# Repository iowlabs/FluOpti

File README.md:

# FluOpti
Este proyecto consiste en la realización de un control integrado para la iluminación del proyecto FluOpti. Más información respecto al poyecto se puede encontrar en los siguientes enlaces:
1. https://docs.google.com/document/d/1PmyignsIkzQdomBdSQQ2lFlBKneosc83GTr52-iTTBQ/edit?usp=sharing
2. [Git](https://github.com/SynBioUC/FluoPi/tree/master/Hardware_design_files/PCB)
3. [OSF](https://osf.io/dy6p2/)
4. [Manual de diseño de proyectos de LEDs estandar](https://www.overleaf.com/4759732231nspqcngnnhdq)

## Descripción de problema electrónico
El sistema consiste en un dispositivo que permite observar muestras biológicas, a las cuales se les realizan procesos de activación genética por medio de otpogenética. 
En la práctica, el dispositivo consiste en una cámara conectada a una raspberry, la que permite observar las muestras, un set de LEDs, los que permiten realizar los procesos optogenéticos, y la respectiva electrónica de control. 

Los LEDs que se deben controlar realizan 3 tareas distintas:
1. Excitar la muestra para poder adquirir imágenes de fluorescencia: LEDs azules.
2. Iluminar la muestra para obtener imágenes de campo claro que permitan medir el crecimiento de las colonias bacterianas de manera apropiada: LEDs blancos.
3. Generar estímulos para activación de procesos optogenéticos. Estos LEDs son de longitudes de onda específicas dependiendo del gen que se desee activar/desactivar: LEDs rojos y verdes.

El proyecto también considera la necesidad de implementar sensores que permitan calibrar el sistema y monitorear variables determinadas, tales como intensidad o temperatura.

## Requerimientos

### Requerimientos generales
A continuación se enlista un set de requerimientos generales del proyecto:
1. Implementar una electrónica compatible con los componentes actuales disponibles.
2. Proponer una solución completa al problema.
3. Considerar diseños modulares que permitan adaptarse a parámetros futuros.

### Requerimientos específicos

A continuación se enlista un set de requerimientos específicos del proyecto:
1. Los LEDs azules empleados para iluminar la muestra corresponden a los [Super Bright 5mm Blue](https://www.superbrightleds.com/moreinfo/through-hole/5mm-blue-led-120-degree-viewing-angle-flat-tipped-1200-mcd/265/1192/):
   * Longitud de onda: 470nm
   * Forward current: 30mA @ 3.3V
   * Peak forward current: 100mA
   * Max voltage forward: 3.8V
   
2. Actualmente, se está pensando en una placa de LEDs azules con distribución física del tipo circular. Esto implicaría una cantidad de 55 LEDs. En la siguiente imagen se muestra esta topología propuesta:

3. Los LEDs verdes empleados para la activación de genes corresponden a los [Kingbright WP7083ZGD/G](http://www.kingbrightusa.com/images/catalog/SPEC/WP7083ZGD-G.pdf):
   * Longitud de onda: 520nm
   * Forward current (typ): 20mA @ 3.2V
   * Peak forward current: 100mA
   * Max voltage forward: 4V
   
4. Los LEDs rojos empleados para la desactivación de genes corresponden a los [Deep-Red 5mm LED](https://www.ledsupply.com/leds/5mm-led-deep-red-660nm-50-degree-viewing-angle):
   * Longitud de onda: 660nm
   * Forward current (typ): 20mA @ 2.2V
   * Peak forward current: 100mA
   * Max voltage forward: 2.8V
   
5. Los LEDs blancos se implementan por medio de una tira LED comercial. Típicamente su operación se caracteriza por:
   * Forward current: 20mA @ 12V
   
6. El control implementado debe corresponder a PWM, con el fin de regular la intensidad lumínica de los LEDs. Se opta por este control debido a su sencilla implementación.

7. El sistema  debe contar con un sistema de distribución de potencia para alimentar todos los sub-módulos, LEDs y raspberry.

8. El sistema debe contar, además, con la posibilidad de leer sensores que permitan medir y calibrar la intensidad de luz proveniente desde los LEDs. Dado que el control se implementa por medio de una raspberry, es necesario utilizar sensores digitales o incluir en el diseño un ADC que permita realizar la conversión. En este último caso será necesaria la inclusión de una etapa que acondicione las señales provenientes desde los sensores.
   
9. El sensor de intensidad lumínica tiene que cumplir:
* Bajo costo
* Fácil de conseguir
* Respuesta plana para los LED Rojo y Verde

Una alternativa es el fototransistor [TEMT6000](https://learn.sparkfun.com/tutorials/temt6000-ambient-light-sensor-hookup-guide/all).

10. El sensor de temperatura es un NTC (termistor). [Aquí](https://www.adafruit.com/product/372) se presenta una alternativa.

11. El heater es del tipo resistivo y se debe poder alimentar con 9V ó 12V. Se debe implementar un control PWM de corriente utilizando un transistor. Una posible alternativa de heater es el [Film Heating Panel](http://www.icstation.com/heating-thin-film-polyimide-heating-plate-panel-25x50mm-b1221-p-9887.html).

### Consideraciones de diseño adicionales
   
1. Consideraciones de operación: El dispositivo debe ser diseñado para funcionar en espacios interiores y dentro de una cápsula cerrada, en la se realiza el análisis de las muestras, por lo que no es necesaria la resistencia al agua o a condiciones de humedad extremas. La placa estará, además, dentro de una caja, por lo que tampoco estará expuesta a polvo u otros contaminantes. Una vez instalado el dispositivo, este permanecerá siempre en el mismo lugar (a menos que se deba extraer por alguna situación en particular), por lo que no es necesario que el diseño considere la exposición a posibles golpes o vibraciones muy significativas.

2. La única etapa del circuito que puede significar un peligro para el usuario es la alimentación, puesto que esta proviene desde la red eléctrica, por lo cual es prudente que la carcasa del producto cumpla con normas acorde al voltaje y corriente de operación, por ejemplo, IP67. Sin embargo, esta protección será ajena al circuito mismo. Es pertinente, de todas formas, la inclusión de disipadores en algunos integrados, en el caso que operen con altas corrientes. Esto, para evitar fallas durante la operación o incluso que se quemen componentes.

## Propuesta
Teniendo presente los requerimientos planteados en la sección anterior se propone una solución basada en el siguiente esquema

El principal criterio de diseño considerado es la modularidad, con el objetivo de poder entregar una solución adaptable y escalable. Los parámetros prácticos de elección de componentes dependen de los requerimientos específicos del sistema. El esquema general consiste en un módulo que genera señales PWM, el cual es controlado por protocolo serial I2C. Este módulo genera 16 señales de PWM permitiendo controlar hasta 16 canales. Estas señales PWM controlan los módulos driver. Estos últimos ajustan la señal PWM a los requerimientos que necesitan los distintos tipos de circuitos de LEDs. Cada driver puede poseer uno o más canales dependiendo de la cantidad de subcircuitos independientes que se deseen controlar por tipo de LED. Del mismo modo, algunas de estas señales de control PWM pueden dejarse a disposición del usuario en caso que necesite controlar una placa con driver ya existente, como es el caso de este proyecto. 

El otro bloque importante es el sistema de distribución de poder, el cual se encarga de generar todos los voltajes necesarios para los distintos bloques y etapas del circuito, dependiendo de cada requerimiento. La idea principal es que la placa reciba una única alimentación y que, internamente, genere los distintos voltajes y corrientes, contribuyendo, así, a la adaptabilidad de la solución.

Por último, la placa considera la inclusión de un ADC de 4 canales, controlado por I2C, el cual permite leer hasta 4 sensores analógicos. Es necesario contar con un ADC, ya que la Raspberry Pi no cuenta con ADC. Esto permite otorgar una alta adaptabilidad, ya que es posible conectar distintos tipos de sensores analógicos, dependiendo de la aplicación. Para esto, la placa considera etapas de acondicionamiento de señal, las cuales se deben configurar para el sensor específico.

### Resumen de características de la solución propuesta

Las principales características de la solución propuesta son:

1. Adaptabilidad: La placa total solo se controla por medio de un bus I2C (3 pines), independiente de la cantidad de LEDs y sensores que se deseen utilizar. 

2. Integración: La disposición de canales de control PWM permite integrar tanto las soluciones existentes como soluciones creadas por distintos fabricantes.

3. Escalabilidad: Gracias a la utilización del protocolo I2C, es posible controlar múltiples de estas placas con una sola Raspberry Pi (o un solo microcontrolador/procesador en general). Si se integran dos placas en serie se puede llegar a disponer de 32 canales de control de LEDs y 8 canales de sensores analógicos. 

A continuación, se describen en detalle los módulos a implementar. Es importante mencionar que se utilizó como guía el [documento tutorial](https://www.overleaf.com/4759732231nspqcngnnhdq) generado en el marco de este proyecto.

### Detalle de módulos

#### ADC
El ADC escogido es el [ADC](https://cdn-shop.adafruit.com/datasheets/ads1115.pdf) de la empresa Texas Instruments. La empresa [adafruit](https://www.adafruit.com/product/1085) posee un módulo autocontenido para integrar este ADC a la Raspberry Pi, así como una completa documentación y las bibliotecas para utilizarlo. 

Las principales características de este ADC se enlistan a continuación

* 4 canales, single-ended.
* 16 bits de resolución
* Voltaje de alimentación entre 2V a 5V
* Interfaz I2C
* Referencia interna

#### Acondicionamiento de señal
Los sensores que se utilizarán permiten implementar el proceso de medición gracias a la variación de sus propiedades eléctricas. En general, estas variaciones se evidencian mediante un cambio de voltaje. En consecuencia, este es el voltaje que debe ser adquirido por el circuito electrónico. Por ello, en primera instancia, se dispone de un circuito divisor que, al ser conectado con el respectivo sensor, permite obtener el voltaje asociado a la medición. En la siguiente figura se muestra un ejemplo de esta conexión circuital, para el caso de un sensor de temperatura del tipo termistor (NTC):

Para realizar correctamente la adquisición de las señales desde los sensores es necesario contar con una etapa de acondicionamiento de señal. De esta forma, se asegura que los valores de voltaje que entreguen los sensores se encuentren dentro de los límites que permiten las entradas del ADC y de la Raspberry. No solo es deseable que se opere dentro de los límites, sino también aprovechar el rango de lectura al máximo, es decir, que el voltaje mínimo de medición sea igual (o lo más cercano posible) al voltaje mínimo que permiten los pines del ADC. Y, la misma relación con el voltaje máximo de medición. 

Dado que aún no existe 100% de certeza sobre los sensores a utilizar, se implementó una circuito genérico de acondicionamiento, el cual se compone de una etapa de amplificación y otra de adición de offset. En la siguiente figura se muestra este circuito:

Los símbolos de switches corresponden, en la práctica, a un solder jumper, el cual conecta la entrada con la salida solo si se unen con soldadura sus terminales. Si se conectan S1, S2 y S3 el circuito queda configurado como un buffer, lo cual, de todas formas, beneficia a la señal adquirida puesto que el buffer disminuye su impedancia. Conectando o no S1, S2 y S3 se pueden obtener distintas configuraciones: solo amplificador, solo adición de offset, o ambas. Además, los valores de las resistencias se pueden ajustar dependiendo de los sensores que se utilicen, de tal forma de fijar correctamente la ganancia y el offset, según sea el caso.

#### Generador de PWM
La generación de PWM se realiza por medio de un circuito integrado [PCA9685](https://cdn-shop.adafruit.com/datasheets/PCA9685.pdf). La empresa [adafruit](https://www.adafruit.com/product/2928) posee un módulo autocontenido para integrar este módulo a la Raspberry Pi, así como una documentación completa y las bibliotecas para utilizarlo. 

Principales características:

* 16 canales dimeables por PWM.
* 12 bits de resolución
* Voltaje de alimentación etre 2.3V a 5.5V
* Interfaz I2C

#### Driver de baja corriente

Para los canales de bajo consumo de corriente, tales como los arreglos de LEDs rojos y verdes, se utilizará el integrado [ULN2803](https://www.electroschematics.com/wp-content/uploads/2013/07/uln2803a-datasheet.pdf). Este integrado implementa un arreglo de 8 transistores tipo darlington, haciendo posible el control de hasta 8 canales en un único integrado.

Principales características:

* Arreglo de 8 canales
* Poseen alimentación común
* La corriente máxima por canal es de 500mA, pudiendo aumentar esta cantidad si se consideran canales en paralelo.

#### Driver de alta corriente
Para los canales de alto consumo se utilizará un transistor mosfet [IRF740](https://datasheet.lcsc.com/szlcsc/1808281645_Infineon-Technologies-IRF7402TRPBF_C169089.pdf). Es necesario contar con un transistor por canal. Y, para casos de alta corriente (superiores a 1A) es necesario considerar la inclusión de disipadores (heatsink) o pads de disipación que permitan una evacuación efectiva del calor.

Principales características:

* Altas frecuencias de switching
* Bajo consumo de operación 
* Control de hasta 10A (ó 40A en corrientes pulsantes)
* Simple implementación

#### Sistema de distribución de poder

Como se mencionará más adelante, la alimentación que llegará al circuito electrónico implementado será de 12VDC, por lo que es necesario contar con convertidores de voltaje DC-DC para generar los distintos voltajes de alimentación que se requieren en el circuito. En particular, es necesario generar 5V y 3.3V para alimentar los circuitos analógicos y digitales, y un set de voltajes para alimentar los distintos arreglos de LEDs y el Heater. Se decidió disponer de los siguientes voltajes para este último uso: 9V, 16V, 20V y 24V. A continuación se especifican los convertidores empleados para generar cada uno de los voltajes mencionados.

##### 5V
* Integrado: [LM2596R-5.0](https://datasheet.lcsc.com/szlcsc/1811131510_HTC-Korea-TAEJIN-Tech-LM2596R-5-0_C77782.pdf)
* Tipo: Step-down, regulador switching
* Frecuencia de switcheo: 150kHz
* Corriente máxima de salida: 3A

##### 3.3V
* Integrado: [AP2112K-3.3](https://datasheet.lcsc.com/szlcsc/1809192242_Diodes-Incorporated-AP2112K-3-3TRG1_C51118.pdf)
* Tipo: LDO, regulador lineal
* Corriente máxima de salida: 600mA

##### 9V
* Integrado: [LM2696SX-ADJ](https://datasheet.lcsc.com/szlcsc/1809192335_Texas-Instruments-LM2596SX-ADJ-NOPB_C29781.pdf)
* Tipo: Step-down, regulador switching ajustable (voltaje de salida es configurable según indicaciones de conexión en el datasheet)
* Frecuencia de switcheo: 150kHz
* Corriente máxima de salida: 3A

##### 16V, 20V, 24V
* Integrado: [XL6008E1](https://datasheet.lcsc.com/szlcsc/1809200019_XLSEMI-XL6008E1_C73012.pdf)
* Tipo: Step-up, regulador switching ajustable (voltaje de salida es configurable según indicaciones de conexión en el datasheet)
* Frecuencia de switcheo: 400kHz
* Corriente máxima de salida: 3A

#### Fuente de alimentación

Dado que el circuito electrónico funcionará con alimentación DC es necesario emplear una fuente DC que se enchufe directamente a la red y que entegue un voltaje de salida continuo. En particular, se decidió emplear una [fuente DC conmutada](https://afel.cl/producto/fuente-de-poder-12v-10a-120w/). Sus principales características son:

* Voltaje de entrada: 100-120VAC / 60Hz, **200-240VAC / 50Hz**
* Voltaje de salida: 12V
* Corriente máxima de salida: 10A
* Potencia máxima de salida: 120W

## Esquemático

En la siguiente figura se muestra el diagrama de bloques del esquemático implementado

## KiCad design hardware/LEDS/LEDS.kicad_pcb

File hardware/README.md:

# FluOpti Electrónica

FluOpti es una dispositivo controlador de LEDs para aplicaciones optogenéticas dentro del contexto del proyecto FluOpti.

La placa desarrollada contiene la electrónica necesaria para controlar fuentes de iluminación de alto consumo basadas en LEDS. Dependiendo de la cantidad de LEDs utilizadas y el tipo de conexión en que se dispongan estas matrices de LEDs pueden variar tanto en consumo como el el voltaje de operación.

Es por esto que la electrónica diseñada fue desarrollada considerando flexibilidad en su implementación para abordar un gran  numero de escenarios.

Cuenta con 4 canales de alta potencia para aborar cargas de 24 20 16 12 V configurables y potencias de ahasta

### Features

 La placa cuenta principalmente con 4 canales para controlar canales de LEDS

 - Canal de alta potencia para LEDs azules
 - 3 canales de baja potencia para LEDs Rojos, Verdes, Blancas.

Adicionalmente la placa implementa un controlador de temperatura, para esto cuenta con la electrónica necesaria para drivear 2 heaters resistivos, y con la capacidad de conectar hasta 4 sensores de temperatura NTC analógicos.

## Descripción de Hardware

El esquema presentado en la siguiente figura presenta una descripción general de la estructura del hardware desarrollado.  

El principal criterio de diseño considerado es la modularidad, con el objetivo de poder entregar una solución adaptable y escalable. El esquema general consiste en un módulo que genera señales PWM, el cual es controlado por protocolo serial I2C. Este módulo genera 16 señales de PWM permitiendo controlar hasta 16 canales. Estas señales PWM controlan los módulos driver que se encargan de adaptarse a los requerimientos de corriente y voltaje de las cargas asociadas. Cada driver puede poseer uno o más canales dependiendo de la cantidad de subcircuitos independientes que se deseen controlar por tipo de LED. Del mismo modo, algunas de estas señales de control PWM fueron dejadas a disposición del usuario en caso que necesite controlar una placa con driver ya existente, como es el caso de este proyecto (compatibilidad con diseños anteriores).

El otro bloque importante es el sistema de distribución de poder, el cual se encarga de generar todos los voltajes necesarios para los distintos bloques y etapas del circuito, dependiendo de cada requerimiento. La idea principal es que la placa reciba una única alimentación y que, internamente, genere los distintos voltajes y corrientes, contribuyendo, así, a la adaptabilidad de la solución.

Por último, la placa considera la inclusión de un ADC de 4 canales, controlado por I2C, el cual permite leer hasta 4 sensores analógicos para implementar los sensores de corriente. Es necesario contar con un ADC, ya que la Raspberry Pi no cuenta con ADC. Esto permite otorgar una alta adaptabilidad, ya que es posible conectar distintos tipos de sensores analógicos, dependiendo de la aplicación. Para esto, la placa considera etapas de acondicionamiento de señal, las cuales se deben configurar para el sensor específico.

### Resumen de características de la solución propuesta

Las principales características de la solución propuesta son:

1. Adaptabilidad: La placa total solo se controla por medio de un bus I2C (3 pines), independiente de la cantidad de LEDs y sensores que se deseen utilizar.

2. Integración: La disposición de canales de control PWM permite integrar tanto las soluciones existentes como soluciones creadas por distintos fabricantes.

3. Escalabilidad: Gracias a la utilización del protocolo I2C, es posible controlar múltiples de estas placas con una sola Raspberry Pi (o un solo microcontrolador/procesador en general). Si se integran dos placas en serie se puede llegar a disponer de 32 canales de control de LEDs y 8 canales de sensores analógicos.

A continuación, se describen en detalle los módulos a implementar. Es importante mencionar que se utilizó como guía el [documento tutorial](https://www.overleaf.com/4759732231nspqcngnnhdq) generado en el marco de este proyecto.

### Detalle de módulos

#### ADC
El ADC escogido es el [ADC](https://cdn-shop.adafruit.com/datasheets/ads1115.pdf) de la empresa Texas Instruments. La empresa [adafruit](https://www.adafruit.com/product/1085) posee un módulo autocontenido para integrar este ADC a la Raspberry Pi, así como una completa documentación y las bibliotecas para utilizarlo.

Las principales características de este ADC se enlistan a continuación

* 4 canales, single-ended.
* 16 bits de resolución
* Voltaje de alimentación entre 2V a 5V
* Interfaz I2C
* Referencia interna

#### Acondicionamiento de señal
Los sensores que se utilizarán permiten implementar el proceso de medición gracias a la variación de sus propiedades eléctricas. En general, estas variaciones se evidencian mediante un cambio de voltaje. En consecuencia, este es el voltaje que debe ser adquirido por el circuito electrónico. Por ello, en primera instancia, se dispone de un circuito divisor que, al ser conectado con el respectivo sensor, permite obtener el voltaje asociado a la medición. En la siguiente figura se muestra un ejemplo de esta conexión circuital, para el caso de un sensor de temperatura del tipo termistor (NTC):

Para realizar correctamente la adquisición de las señales desde los sensores es necesario contar con una etapa de acondicionamiento de señal. De esta forma, se asegura que los valores de voltaje que entreguen los sensores se encuentren dentro de los límites que permiten las entradas del ADC y de la Raspberry. No solo es deseable que se opere dentro de los límites, sino también aprovechar el rango de lectura al máximo, es decir, que el voltaje mínimo de medición sea igual (o lo más cercano posible) al voltaje mínimo que permiten los pines del ADC. Y, la misma relación con el voltaje máximo de medición.

Dado que aún no existe 100% de certeza sobre los sensores a utilizar, se implementó una circuito genérico de acondicionamiento, el cual se compone de una etapa de amplificación y otra de adición de offset. En la siguiente figura se muestra este circuito:

Los símbolos de switches corresponden, en la práctica, a un solder jumper, el cual conecta la entrada con la salida solo si se unen con soldadura sus terminales. Si se conectan S1, S2 y S3 el circuito queda configurado como un buffer, lo cual, de todas formas, beneficia a la señal adquirida puesto que el buffer disminuye su impedancia. Conectando o no S1, S2 y S3 se pueden obtener distintas configuraciones: solo amplificador, solo adición de offset, o ambas. Además, los valores de las resistencias se pueden ajustar dependiendo de los sensores que se utilicen, de tal forma de fijar correctamente la ganancia y el offset, según sea el caso.

#### Generador de PWM
La generación de PWM se realiza por medio de un circuito integrado [PCA9685](https://cdn-shop.adafruit.com/datasheets/PCA9685.pdf). La empresa [adafruit](https://www.adafruit.com/product/2928) posee un módulo autocontenido para integrar este módulo a la Raspberry Pi, así como una documentación completa y las bibliotecas para utilizarlo.

Principales características:

* 16 canales dimeables por PWM.
* 12 bits de resolución
* Voltaje de alimentación etre 2.3V a 5.5V
* Interfaz I2C

#### Driver de baja corriente

Para los canales de bajo consumo de corriente, tales como los arreglos de LEDs rojos y verdes, se utilizará el integrado [ULN2803](https://www.electroschematics.com/wp-content/uploads/2013/07/uln2803a-datasheet.pdf). Este integrado implementa un arreglo de 8 transistores tipo darlington, haciendo posible el control de hasta 8 canales en un único integrado.

Principales características:

* Arreglo de 8 canales
* Poseen alimentación común
* La corriente máxima por canal es de 500mA, pudiendo aumentar esta cantidad si se consideran canales en paralelo.

#### Driver de alta corriente
Para los canales de alto consumo se utilizará un transistor mosfet [IRF740](https://datasheet.lcsc.com/szlcsc/1808281645_Infineon-Technologies-IRF7402TRPBF_C169089.pdf). Es necesario contar con un transistor por canal. Y, para casos de alta corriente (superiores a 1A) es necesario considerar la inclusión de disipadores (heatsink) o pads de disipación que permitan una evacuación efectiva del calor.

Principales características:

* Altas frecuencias de switching
* Bajo consumo de operación
* Control de hasta 10A (ó 40A en corrientes pulsantes)
* Simple implementación

#### Sistema de distribución de poder

Como se mencionará más adelante, la alimentación que llegará al circuito electrónico implementado será de 12VDC, por lo que es necesario contar con convertidores de voltaje DC-DC para generar los distintos voltajes de alimentación que se requieren en el circuito. En particular, es necesario generar 5V y 3.3V para alimentar los circuitos analógicos y digitales, y un set de voltajes para alimentar los distintos arreglos de LEDs y el Heater. Se decidió disponer de los siguientes voltajes para este último uso: 9V, 16V, 20V y 24V. A continuación se especifican los convertidores empleados para generar cada uno de los voltajes mencionados.

##### 5V
* Integrado: [LM2596R-5.0](https://datasheet.lcsc.com/szlcsc/1811131510_HTC-Korea-TAEJIN-Tech-LM2596R-5-0_C77782.pdf)
* Tipo: Step-down, regulador switching
* Frecuencia de switcheo: 150kHz
* Corriente máxima de salida: 3A

##### 3.3V
* Integrado: [AP2112K-3.3](https://datasheet.lcsc.com/szlcsc/1809192242_Diodes-Incorporated-AP2112K-3-3TRG1_C51118.pdf)
* Tipo: LDO, regulador lineal
* Corriente máxima de salida: 600mA

##### 9V
* Integrado: [LM2696SX-ADJ](https://datasheet.lcsc.com/szlcsc/1809192335_Texas-Instruments-LM2596SX-ADJ-NOPB_C29781.pdf)
* Tipo: Step-down, regulador switching ajustable (voltaje de salida es configurable según indicaciones de conexión en el datasheet)
* Frecuencia de switcheo: 150kHz
* Corriente máxima de salida: 3A

##### 16V, 20V, 24V
* Integrado: [XL6008E1](https://datasheet.lcsc.com/szlcsc/1809200019_XLSEMI-XL6008E1_C73012.pdf)
* Tipo: Step-up, regulador switching ajustable (voltaje de salida es configurable según indicaciones de conexión en el datasheet)
* Frecuencia de switcheo: 400kHz
* Corriente máxima de salida: 3A

#### Fuente de alimentación

Dado que el circuito electrónico funcionará con alimentación DC es necesario emplear una fuente DC que se enchufe directamente a la red y que entegue un voltaje de salida continuo. En particular, se decidió emplear una [fuente DC conmutada](https://afel.cl/producto/fuente-de-poder-12v-10a-120w/). Sus principales características son:

* Voltaje de entrada: 100-120VAC / 60Hz, **200-240VAC / 50Hz**
* Voltaje de salida: 12V
* Corriente máxima de salida: 10A
* Potencia máxima de salida: 120W

## Esquemático

En la siguiente figura se muestra el diagrama de bloques del esquemático implementado

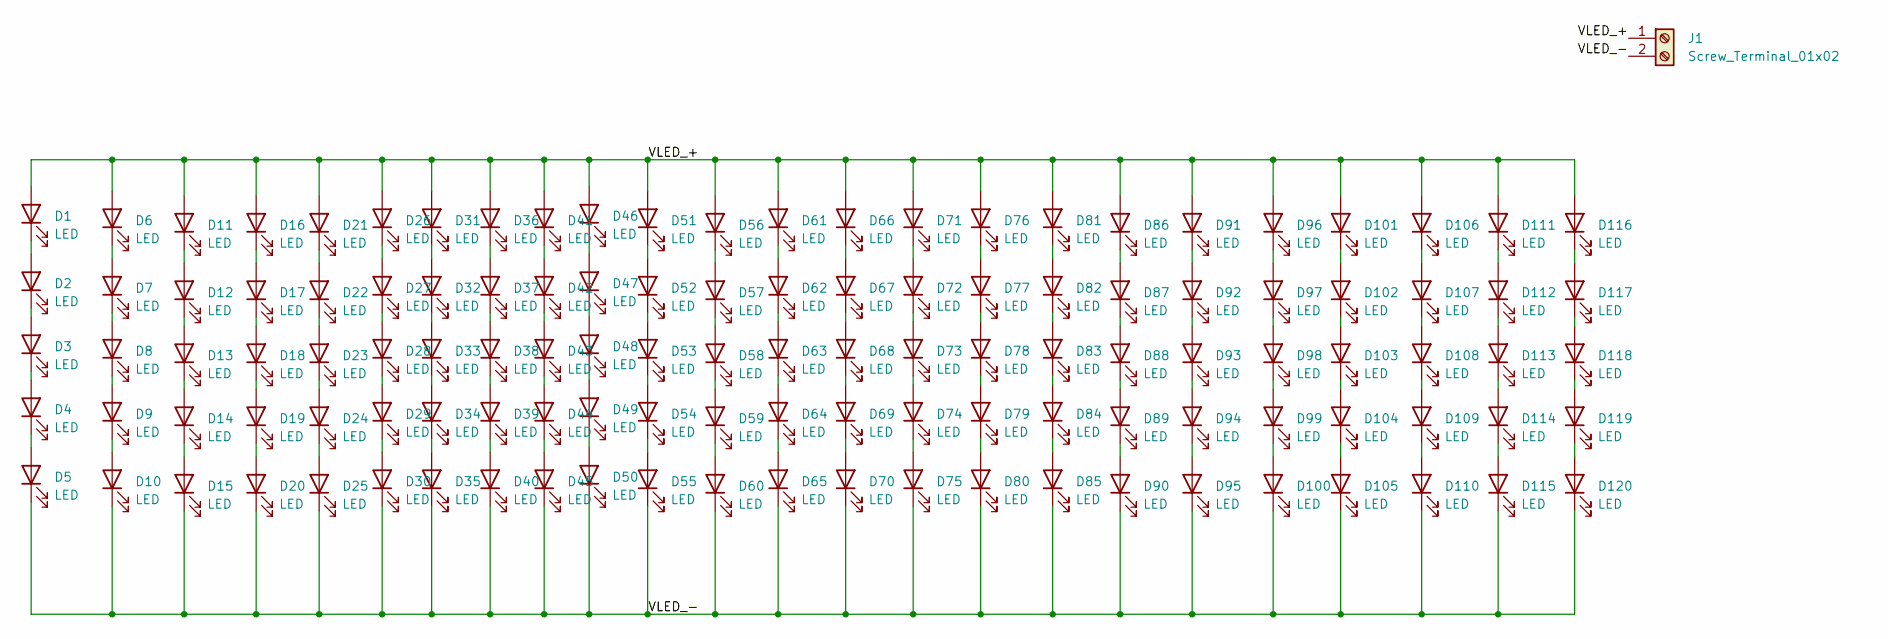
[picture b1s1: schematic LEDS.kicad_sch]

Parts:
D1, D2, D3, D4, D5, D6, D7, D8, D9, D10, D11, D12, D13, D14, D15, D16, D17, D18, D19, D20, D21, D22, D23, D24, D25, D26, D27, D28, D29, D30, D31, D32, D33, D34, D35, D36, D37, D38, D39, D40, D41, D42, D43, D44, D45, D46, D47, D48, D49, D50, D51, D52, D53, D54, D55, D56, D57, D58, D59, D60, D61, D62, D63, D64, D65, D66, D67, D68, D69, D70, D71, D72, D73, D74, D75, D76, D77, D78, D79, D80, D81, D82, D83, D84, D85, D86, D87, D88, D89, D90, D91, D92, D93, D94, D95, D96, D97, D98, D99, D100, D101, D102, D103, D104, D105, D106, D107, D108, D109, D110, D111, D112, D113, D114, D115, D116, D117, D118, D119, D120: LED; LED_D5.0mm_FlatTop
J1: Screw_Terminal_01x02; Tb-2x1-5p-TH-V

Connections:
/VLED_+: D1.2 (A), D6.2 (A), D11.2 (A), D16.2 (A), D21.2 (A), D26.2 (A), D31.2 (A), D36.2 (A), D41.2 (A), D46.2 (A), D51.2 (A), D56.2 (A), D61.2 (A), D66.2 (A), D71.2 (A), D76.2 (A), D81.2 (A), D86.2 (A), D91.2 (A), D96.2 (A), D101.2 (A), D106.2 (A), D111.2 (A), D116.2 (A), J1.1
/VLED_-: D5.1 (K), D10.1 (K), D15.1 (K), D20.1 (K), D25.1 (K), D30.1 (K), D35.1 (K), D40.1 (K), D45.1 (K), D50.1 (K), D55.1 (K), D60.1 (K), D65.1 (K), D70.1 (K), D75.1 (K), D80.1 (K), D85.1 (K), D90.1 (K), D95.1 (K), D100.1 (K), D105.1 (K), D110.1 (K), D115.1 (K), D120.1 (K), J1.2
unnamed: D1.1 (K), D2.2 (A)
unnamed: D2.1 (K), D3.2 (A)
unnamed: D3.1 (K), D4.2 (A)
unnamed: D4.1 (K), D5.2 (A)
unnamed: D6.1 (K), D7.2 (A)
unnamed: D7.1 (K), D8.2 (A)
unnamed: D8.1 (K), D9.2 (A)
unnamed: D9.1 (K), D10.2 (A)
unnamed: D11.1 (K), D12.2 (A)
unnamed: D12.1 (K), D13.2 (A)
unnamed: D13.1 (K), D14.2 (A)
unnamed: D14.1 (K), D15.2 (A)
unnamed: D16.1 (K), D17.2 (A)
unnamed: D17.1 (K), D18.2 (A)
unnamed: D18.1 (K), D19.2 (A)
unnamed: D19.1 (K), D20.2 (A)
unnamed: D21.1 (K), D22.2 (A)
unnamed: D22.1 (K), D23.2 (A)
unnamed: D23.1 (K), D24.2 (A)
unnamed: D24.1 (K), D25.2 (A)
unnamed: D26.1 (K), D27.2 (A)
unnamed: D27.1 (K), D28.2 (A)
unnamed: D28.1 (K), D29.2 (A)
unnamed: D29.1 (K), D30.2 (A)
unnamed: D31.1 (K), D32.2 (A)
unnamed: D32.1 (K), D33.2 (A)
unnamed: D33.1 (K), D34.2 (A)
unnamed: D34.1 (K), D35.2 (A)
unnamed: D36.1 (K), D37.2 (A)
unnamed: D37.1 (K), D38.2 (A)
unnamed: D38.1 (K), D39.2 (A)
unnamed: D39.1 (K), D40.2 (A)
unnamed: D41.1 (K), D42.2 (A)
unnamed: D42.1 (K), D43.2 (A)
unnamed: D43.1 (K), D44.2 (A)
unnamed: D44.1 (K), D45.2 (A)
unnamed: D46.1 (K), D47.2 (A)
unnamed: D47.1 (K), D48.2 (A)
unnamed: D48.1 (K), D49.2 (A)
unnamed: D49.1 (K), D50.2 (A)
unnamed: D51.1 (K), D52.2 (A)
unnamed: D52.1 (K), D53.2 (A)
unnamed: D53.1 (K), D54.2 (A)
unnamed: D54.1 (K), D55.2 (A)
unnamed: D56.1 (K), D57.2 (A)
unnamed: D57.1 (K), D58.2 (A)
unnamed: D58.1 (K), D59.2 (A)
unnamed: D59.1 (K), D60.2 (A)
unnamed: D61.1 (K), D62.2 (A)
unnamed: D62.1 (K), D63.2 (A)
unnamed: D63.1 (K), D64.2 (A)
unnamed: D64.1 (K), D65.2 (A)
unnamed: D66.1 (K), D67.2 (A)
unnamed: D67.1 (K), D68.2 (A)
unnamed: D68.1 (K), D69.2 (A)
unnamed: D69.1 (K), D70.2 (A)
unnamed: D71.1 (K), D72.2 (A)
unnamed: D72.1 (K), D73.2 (A)
unnamed: D73.1 (K), D74.2 (A)
unnamed: D74.1 (K), D75.2 (A)
unnamed: D76.1 (K), D77.2 (A)
unnamed: D77.1 (K), D78.2 (A)
unnamed: D78.1 (K), D79.2 (A)
unnamed: D79.1 (K), D80.2 (A)
unnamed: D81.1 (K), D82.2 (A)
unnamed: D82.1 (K), D83.2 (A)
unnamed: D83.1 (K), D84.2 (A)
unnamed: D84.1 (K), D85.2 (A)
unnamed: D86.1 (K), D87.2 (A)
unnamed: D87.1 (K), D88.2 (A)
unnamed: D88.1 (K), D89.2 (A)
unnamed: D89.1 (K), D90.2 (A)
unnamed: D91.1 (K), D92.2 (A)
unnamed: D92.1 (K), D93.2 (A)
unnamed: D93.1 (K), D94.2 (A)
unnamed: D94.1 (K), D95.2 (A)
unnamed: D96.1 (K), D97.2 (A)
unnamed: D97.1 (K), D98.2 (A)
unnamed: D98.1 (K), D99.2 (A)
unnamed: D99.1 (K), D100.2 (A)
unnamed: D101.1 (K), D102.2 (A)
unnamed: D102.1 (K), D103.2 (A)
unnamed: D103.1 (K), D104.2 (A)
unnamed: D104.1 (K), D105.2 (A)
unnamed: D106.1 (K), D107.2 (A)
unnamed: D107.1 (K), D108.2 (A)
unnamed: D108.1 (K), D109.2 (A)
unnamed: D109.1 (K), D110.2 (A)
unnamed: D111.1 (K), D112.2 (A)
unnamed: D112.1 (K), D113.2 (A)
unnamed: D113.1 (K), D114.2 (A)
unnamed: D114.1 (K), D115.2 (A)
unnamed: D116.1 (K), D117.2 (A)
unnamed: D117.1 (K), D118.2 (A)
unnamed: D118.1 (K), D119.2 (A)
unnamed: D119.1 (K), D120.2 (A)

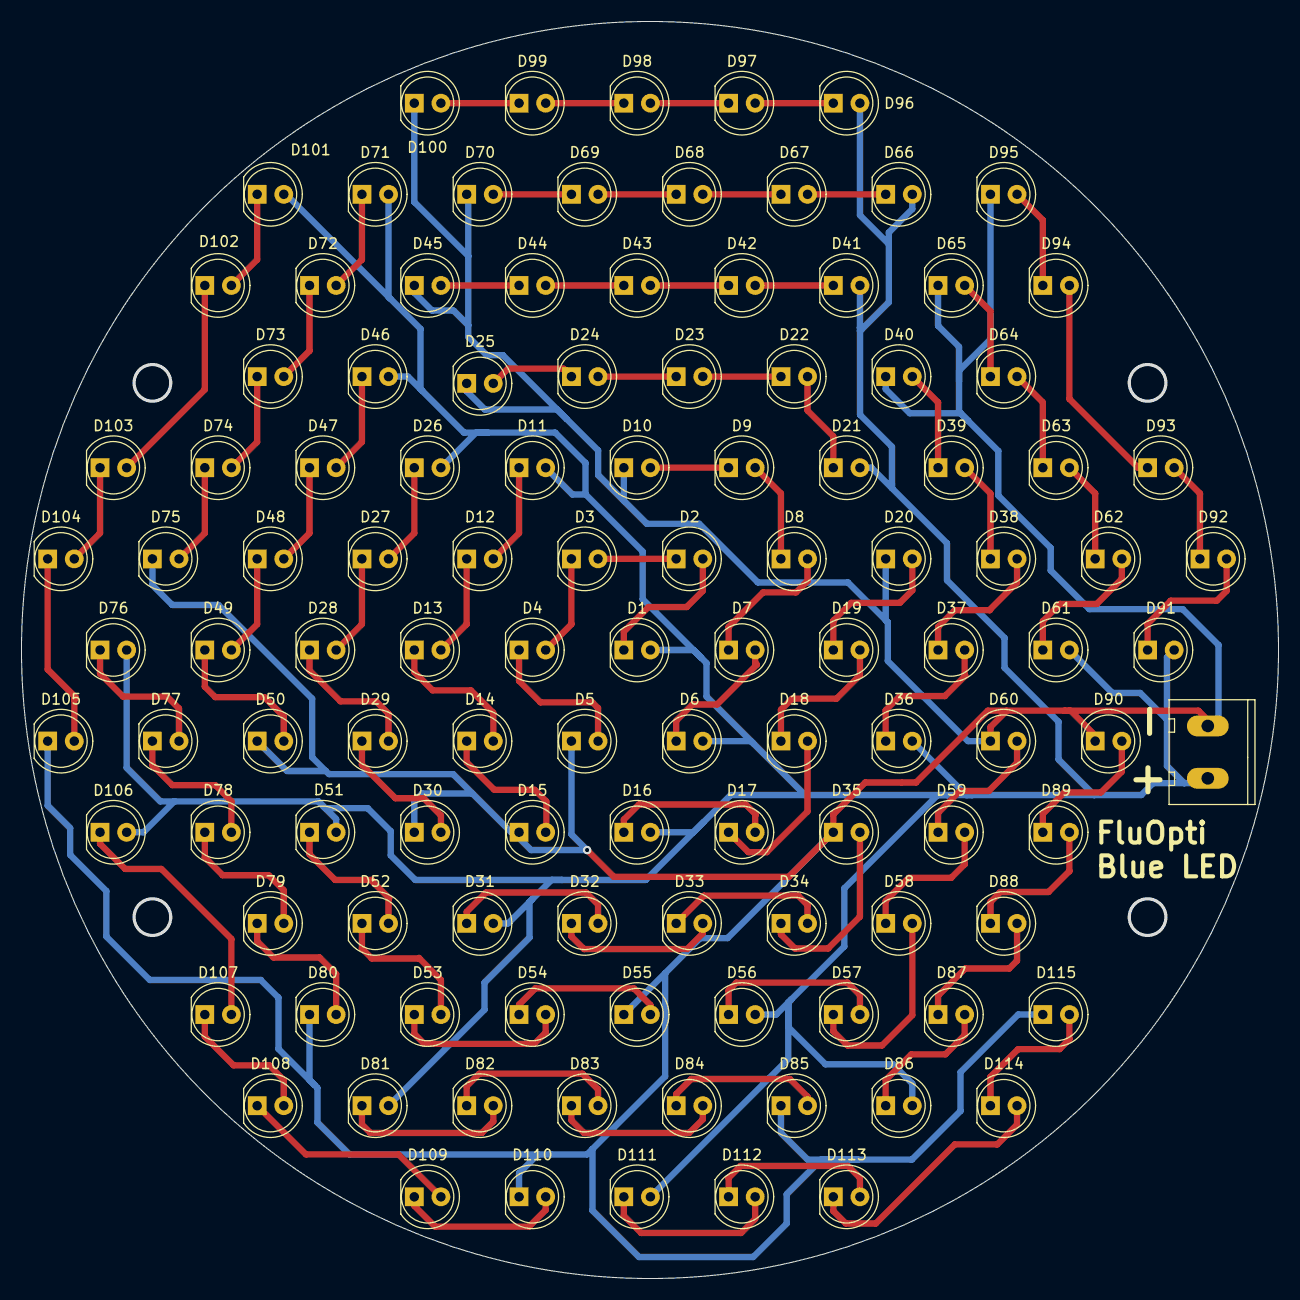
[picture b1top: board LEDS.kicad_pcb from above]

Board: 2 copper layers, 120.0 x 120.0 mm, 116 parts (0 on the bottom side), 94 nets.

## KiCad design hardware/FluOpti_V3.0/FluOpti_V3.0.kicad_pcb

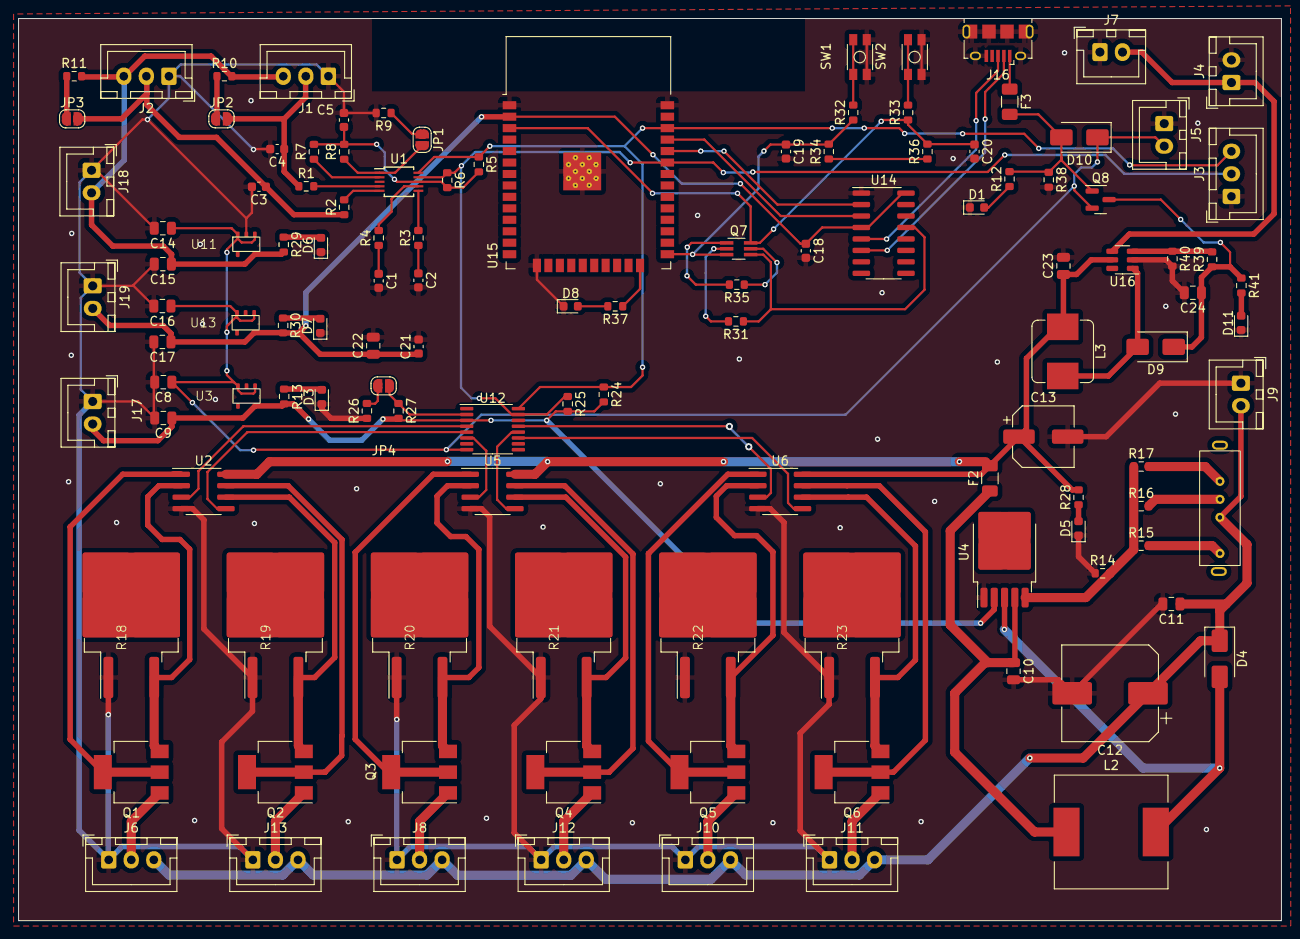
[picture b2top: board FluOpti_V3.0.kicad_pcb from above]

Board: 2 copper layers, 140.0 x 100.0 mm, 121 parts (0 on the bottom side), 80 nets.

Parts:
C1, C2, C3, C4, C5, C18, C19, C20, C21: 100n; C_0603_1608Metric
C8, C9, C10, C11, C14, C15, C16, C17: 1u; C_0805_2012Metric
C12: 220u; CP_Elec_10x10.5
C13: 47u; CP_Elec_6.3x7.7
C22: 10u; C_0805_2012Metric
C23, C24: 22u; C_0805_2012Metric
D1, D3, D5, D6, D7, D8, D11: LED; LED_0603_1608Metric
D4, D9, D10: D_Schottky; D_SMA
F2: Fuse; Fuse_1206_3216Metric
F3: FUSE; Fuse_1206_3216Metric
J1: Sensor1; JST_XH_B3B-XH-A_1x03_P2.50mm_Vertical
J2: Sensor2; JST_XH_B3B-XH-A_1x03_P2.50mm_Vertical
J3: I2C_IN; JST_XH_B3B-XH-A_1x03_P2.50mm_Vertical
J4: PWR_IN; JST_XH_B2B-XH-A_1x02_P2.50mm_Vertical
J5: TP-5V; JST_XH_B2B-XH-A_1x02_P2.50mm_Vertical
J6: LED_1; JST_XH_B3B-XH-A_1x03_P2.50mm_Vertical
J7: TP-PWR_IN; JST_XH_B2B-XH-A_1x02_P2.50mm_Vertical
J8: LED_3; JST_XH_B3B-XH-A_1x03_P2.50mm_Vertical
J9: TP-VCC_H1; JST_XH_B2B-XH-A_1x02_P2.50mm_Vertical
J10: H1; JST_XH_B3B-XH-A_1x03_P2.50mm_Vertical
J11: H2; JST_XH_B3B-XH-A_1x03_P2.50mm_Vertical
J12: LED_4; JST_XH_B3B-XH-A_1x03_P2.50mm_Vertical
J13: LED_2; JST_XH_B3B-XH-A_1x03_P2.50mm_Vertical
J16: USB_B_Micro; USB_Micro-B_Amphenol_10118194_Horizontal
J17: TP-3.3V; JST_XH_B2B-XH-A_1x02_P2.50mm_Vertical
J18: TP-3.3V-Sens; JST_XH_B2B-XH-A_1x02_P2.50mm_Vertical
J19: TP-3.3V-Disp; JST_XH_B2B-XH-A_1x02_P2.50mm_Vertical
JP1, JP2, JP3, JP4: Jumper_2_Open; SolderJumper-2_P1.3mm_Open_RoundedPad1.0x1.5mm
L2: 33u; L_12x12mm_H8mm
L3: 22u; L_Bourns_SRP7028A_7.3x6.6mm
Q1, Q2, Q3, Q4, Q5, Q6: NPN; SOT-223-3_TabPin2
Q7: Q_Dual_NPN_NPN_BRT_E1B1C2E2B2C1; SOT-363_SC-70-6_Handsoldering
Q8: Q_PMOS_GSD; SOT-23
R1, R2, R3, R4: 220; R_0603_1608Metric
R5, R6, R9, R24, R25, R26: 10k; R_0603_1608Metric
R7, R8, R10, R11, R27: 2k; R_0603_1608Metric
R12: 100; R_0603_1608Metric
R13, R29, R30: 10; R_0603_1608Metric
R14, R28: 1k; R_0603_1608Metric
R15: 11.8k; R_0603_1608Metric
R16: 15k; R_0603_1608Metric
R17: 18.2k; R_0603_1608Metric
R18, R19, R20, R21, R22, R23: 5; TO-263-3 TAB 3
R31, R34, R35, R36, R38: 10K; R_0603_1608Metric
R32, R33: 200; R_0603_1608Metric
R37: 330; R_0603_1608Metric
R39: 7K5; R_0603_1608Metric
R40: 1K; R_0603_1608Metric
R41: 470; R_0603_1608Metric
SW1, SW2: SW_DIP_x02; SMD_SWITCH
U1: ADS1115IDGS; TSSOP-10_3x3mm_P0.5mm
U2, U5, U6: TLC272; SOIC-8_3.9x4.9mm_P1.27mm
U3, U11, U13: AP2112K-3.3TRG1; SOT-25
U4: XL6008; TO-252-5_TabPin6
U7: Switch SP3T SS13D07L2B
U12: AD5659R; TSSOP-16_4.4x5mm_P0.65mm
U14: CH340C; SOIC-16_3.9x9.9mm_P1.27mm
U15: ESP32-WROOM-32D; ESP32-WROOM-32
U16: MT3608; SOT-23-6

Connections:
3.3V: C5.1, C9.1, J17.2, R5.2, R6.2, R7.2, R8.2, R13.2, R24.2, R25.2, R27.2, U1.8 (VDD), U3.5 (Vout), U4.2 (EN), U12.3 (Vdd)
3.3V_Disp: C17.1, C18.1, C21.1, C22.1, J19.2, R30.2, U13.5 (Vout), U14.4 (V3), U14.16 (VCC), U15.2 (VDD)
3.3V_Sens: C15.1, J1.3, J2.3, J18.2, R10.2, R11.2, R29.2, U11.5 (Vout)
5V: C8.1, C14.1, C16.1, D10.1 (K), J5.2, Q8.2 (S), U3.1 (Vin), U3.3 (EN), U11.1 (Vin), U11.3 (EN), U12.8 (V_REF), U13.1 (Vin), U13.3 (EN)
5V_IN: C24.1, D9.1 (K), Q8.3 (D), R39.1, R41.1
16V: R15.2, U7.1
20V: R16.2, U7.3
24V: R17.2, U7.4
+3V3: R34.1, R36.1
/DTR#: Q7.4 (E1), R31.1, U14.13 (~DTR)
/FB_5V: R39.2, R40.1, U16.3 (FB)
/IO0: C19.1, Q7.3 (C1), R32.1, R34.2, U15.25 (IO0)
/IO2: R37.1, U15.24 (IO2)
/RESET: C20.1, Q7.6 (C1), R33.1, R36.2, U15.3 (EN)
/RST#: Q7.1 (E1), R35.2, U14.14 (~RTS)
/RX: U14.2 (TXD), U15.34 (RXD0/IO3)
/SW_5V: D9.2 (A), L3.2, U16.1 (SW)
/TX: U14.3 (RXD), U15.35 (TXD0/IO1)
GND: C1.2, C2.2, C3.2, C4.2, C5.2, C8.2, C9.2, C10.2, C11.2, C12.2, C13.2, C14.2, C15.2, C16.2, C17.2, C18.2, C19.2, C20.2, C21.2, C22.2, C23.2, C24.2, D1.1 (K), D3.1 (K), D5.1 (K), D6.1 (K), D7.1 (K), D8.1 (K), D11.1 (K), J1.1, J2.1, J3.1, J4.2, J5.1, J6.1, J7.1, J8.1, J9.1, J10.1, J11.1, J12.1, J13.1, J16.5 (GND), J16.6 (Shield), J17.1, J18.1, J19.1, R9.2, R14.1, R18.1, R19.1, R20.1, R21.1, R22.1, R23.1, R26.1, R38.2, R40.2, SW1.1, SW1.2, SW2.1, SW2.2, U1.3 (GND), U2.4 (V-), U3.2 (GND), U4.1 (GND), U5.4 (V-), U6.4 (V-), U11.2 (GND), U12.14 (GND), U13.2 (GND), U14.1 (GND), U15.1 (GND), U15.15 (GND), U15.38 (GND), U15.39 (GND), U16.2 (GND)
I_H1: J10.2, Q5.1 (C)
I_H2: J11.2, Q6.1 (C)
I_LED_1: J6.2, Q1.1 (C)
I_LED_2: J13.2, Q2.1 (C)
I_LED_3: J8.2, Q3.1 (C)
I_LED_4: J12.2, Q4.1 (C)
unnamed: C1.1, R4.1
unnamed: C2.1, R3.1
unnamed: D1.2 (A), R12.1
unnamed: D3.2 (A), R13.1
unnamed: D4.2 (A), L2.2, U4.3 (SW), U4.6 (TAB)
unnamed: D5.2 (A), R28.1
unnamed: D6.2 (A), R29.1
unnamed: D7.2 (A), R30.1
unnamed: D8.2 (A), R37.2
unnamed: D11.2 (A), R41.2
unnamed: J16.3 (D+), U14.5 (UD+)
unnamed: J16.2 (D-), U14.6 (UD-)
unnamed: F3.1, J16.1 (VBUS)
unnamed: JP1.1 (A), R9.1
unnamed: JP1.2 (B), R8.1, U1.1 (ADDR)
unnamed: JP2.1 (A), R10.1
unnamed: JP3.1 (A), R11.1
unnamed: JP4.1 (A), R27.1, U12.2 (A0)
unnamed: JP4.2 (B), R26.2
unnamed: Q1.2 (B), U2.1
unnamed: Q1.3 (E), R18.2, U2.2 (-)
unnamed: Q2.2 (B), U2.7
unnamed: Q2.3 (E), R19.2, U2.6 (-)
unnamed: Q3.2 (B), U5.1
unnamed: Q3.3 (E), R20.2, U5.2 (-)
unnamed: Q4.2 (B), U5.7
unnamed: Q4.3 (E), R21.2, U5.6 (-)
unnamed: Q5.2 (B), U6.1
unnamed: Q5.3 (E), R22.2, U6.2 (-)
unnamed: Q6.2 (B), U6.7
unnamed: Q6.3 (E), R23.2, U6.6 (-)
unnamed: Q7.5 (B1), R35.1
unnamed: Q7.2 (B1), R31.2
unnamed: R32.2, SW1.3, SW1.4
unnamed: R33.2, SW2.3, SW2.4
unnamed: R1.2, U1.4 (AIN0)
unnamed: R2.2, U1.5 (AIN1)
unnamed: R3.2, U1.6 (AIN2)
unnamed: R4.2, U1.7 (AIN3)
unnamed: R7.1, U1.2 (ALERT/RDY)
unnamed: R14.2, R15.1, R16.1, R17.1, U4.5 (FB)
unnamed: C10.1, F2.1, L2.1, U4.4 (Vin)
SCL: J3.3, R5.1, R24.1, U1.10 (SCL), U12.16 (SCL), U15.36 (IO22)
SDA: J3.2, R6.1, R25.1, U1.9 (SDA), U12.15 (SDA), U15.33 (IO21)
Temp1: C4.1, J1.2, JP2.2 (B), R1.1
Temp2: C3.1, J2.2, JP3.2 (B), R2.1
VCC_H1: C11.1, C12.1, D4.1 (K), J6.3, J8.3, J9.2, J10.3, J11.3, J12.3, J13.3, U7.2
V_H_1: U6.3 (+), U12.13 (V_OUT_B)
V_H_2: U6.5 (+), U12.11 (V_OUT_F)
V_LED_1: U2.3 (+), U12.4 (V_OUT_A)
V_LED_2: U2.5 (+), U12.5 (V_OUT_C)
V_LED_3: U5.3 (+), U12.6 (V_OUT_E)
V_LED_4: U5.5 (+), U12.12 (V_OUT_D)
V_PWR: C13.1, C23.1, F2.2, J4.1, J7.2, L3.1, R28.2, U2.8 (V+), U5.8 (V+), U6.8 (V+), U16.4 (EN), U16.5 (IN)
V_USB: D10.2 (A), F3.2, Q8.1 (G), R12.2, R38.1

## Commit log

2020-09-03 Reupload
2020-09-04 README Images folder
2020-09-04 updated images
2020-12-16 testing Fluopti lib
2020-12-16 fixing pwm module
2020-12-17 test i2c
2020-12-17 fixing dic problem
2020-12-17 time problem
2020-12-23 testing threds
2020-12-23 testing threads
2021-04-09 bom updated
2022-01-05 adding schematics pdf
2022-06-14 wac checkking repo
2023-10-02 working on sample test!
2023-10-02 testing rutintes
2023-11-05 changing the folder order
2023-11-29 Update software-readme.md
    Se completó un poco más la descripción de los preparativos de uso del software
2023-11-29 Update software-readme.md
    se añadieron algunas indicaciones del testeo
2023-12-01 improve simple_test rutine and add get_chan function to FluOpti library
2023-12-01 add test_GPIO.py rutine to use GPIO and FluOpti library together
2023-12-01 add GPIO functions to FluOpti library and update the GPIO test rutine
2023-12-10 rearrange the modules attribute of Fluopti class and improve related functions as well as test. Also add a new rutine to turn ON leds manually
2023-12-10 generalize the function to obtain list of modules based on their properties. Update the test rutines
2023-12-20 simple_test changes
2024-01-08 Update pi_adc.py
    correción de codigo a sensores
2024-01-09 esquematico
2024-01-10 ajustes_esquematico
2024-01-12 modificación
2024-01-15 placa
2024-01-18 esquinas
2024-01-23 pid funcional
    cambios en librerias realizados para su funcionamiento
2024-01-24 adding gui v1
2024-01-24 workink on adc module
2024-01-24 interfaz en FluOpti
    adaptado a minifluopti y fluopti
2024-01-26 modificacion_pcb
2024-01-29 minor corrections to FluOpty.py
2024-01-29 correct some minor merge discrepances
2024-02-12 Nueva_interfaz y tests
2024-02-12 Nueva version fluopticontrolador para pruebas
2024-02-12 arreglo_bug_gui
2024-02-12 nueva ventana secuenciador
2024-02-12 fluo_v2_funcional
2024-02-12 adding some documentation
2024-02-13 arreglo bug FluOpti _default_module
2024-02-13 cambio timer updateData
2024-02-13 implementacion de leds en interfaz y tiempo del bloque
2024-02-14 add rutines to capture images and perform tiemlapse. Perform some modifications to FluOpti for that aim. Update some documentation
2024-02-14 Update software readme.md
    correct iamge position and text
2024-02-15 actualización interfaz a raspi
2024-02-15 autor
2024-02-20 Nuevos archivos para cambio en interfaz post reunion
2024-02-21 board v3 minor changes
2024-02-21 ajustes_PCB
2024-02-21 avances nueva gui
2024-02-22 Implementacion de nueva GUI en fluoControlador_v3 y avance en Configuracion de patrones de fotos
2024-02-22 hotfix
2024-02-23 arreglo temporal a LEDoff
2024-02-23 arreglo timer
2024-02-23 comento un timer para debugear mas facil
2024-02-23 Se agrega el configurador de patrones
2024-02-23 debug fotos preview
2024-02-23 debug camera
2024-02-23 fix bug paramtros camera
2024-02-23 preview label
2024-02-23 preview lista
2024-02-23 patrones infinitos
2024-02-25 update some FluOpti.py module details to imporve its compatibility with the input tl_config.txt file. Uptload the tl_config.txt file template-example
2024-02-26 minnor update to tl_config.txt
2024-02-26 cambios pequeños interfaz
2024-02-26 TODOs pendientes
2024-03-15 updating temp control on gui
2024-03-30 adding openSCAD and STLs
2024-04-07 minor corrections to make them work wirh the new FluOpti methods
2024-04-07 change the invalid temperature measurement value from -1 to 100, then the heater stops if this measurement fails
2024-04-07 Update the turn OFF method
2024-04-08 Rename readthedocs.yaml to .readthedocs.yaml
2024-04-08 Update and rename .readthedocs.yaml to not
2024-04-09 change ReadTheDocs folders
2024-04-09 requeriments.txt added
2024-04-09 RST from MD
2024-04-09 add RST
2024-04-09 with image
2024-04-09 image?
2024-04-09 image folders fixed
2024-04-09 cambiecito
2024-04-10 image en source
2024-04-10 Rename Diagrama_1.PNG to diagrama_1.png
2024-04-10 still with image
2024-04-10 toctree issues
2024-04-10 I think I've done it
2024-04-10 I think I've done it now lol
2024-05-31 actualizacion_PCB
2025-03-12 correct openscad
2025-04-07 add separate base
2025-04-24 new designs and STLs folder
